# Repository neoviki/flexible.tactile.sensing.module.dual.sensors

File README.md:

# Flexible Tactile Sensing Module with Dual Sensors

## Description

This project features a **flexible tactile sensing module** equipped with **dual pressure sensors** designed to measure **tactile interaction**, specifically the pressure exerted by external forces. At the core of the module are two **BMP384 barometric pressure sensors** — MEMS (Micro-Electro-Mechanical Systems) sensors capable of measuring both **barometric pressure** and **temperature** with low power consumption. Their sensitivity makes them well-suited for tactile feedback and subtle pressure variation detection.

The **spacing between the two BMP384 sensors** is **3 millimeters**, allowing for localized differential pressure sensing. Both sensors communicate via the **I2C protocol**, ensuring straightforward integration with microcontroller boards such as the **Arduino Due**. The module operates at **3.3V**, and each sensor is assigned a unique I2C address to enable communication on the same bus:

- **Top Sensor**: `0x77`  
- **Bottom Sensor**: `0x76`

This tactile sensing module can be used in robotics, prosthetics, and human-machine interaction applications.

The **sensor module** is designed on a **flexible PCB**, making it adaptable to a wide range of environments where flexibility is essential. The design is created using **Eagle 7.7**, and the board is populated using **surface-mount technology (SMT)**. After population, the board has been tested with an **Arduino Due** to verify its sensor performance and sampling rate for tactile sensing applications.

## Project Structure

```
README.md
01.Documents                            # Essential documents used for this project
02.Schematics.and.Board.Layout.Design   # Contains the schematics and board layout files
03.Manufacturing                        # Contains CAM, DRU files, and other essential files for manufacturing
04.Populated.Board.Testing              # Contains Arduino code to test the tactile sensing module after population
05.Images                               # Contains a list of images
```

### Images

Here are some images related to the project, demonstrating the design and testing process:

1. **Populated Flexible Tactile Sensing Module**  

2. **Board Layout**  

3. **Schematics**  

4. **Fabricated Flexible PCB**  

---

## License

This project is licensed under the **BSD 2-Clause License**.  
See the [`LICENSE`](LICENSE) file for full license text.

## Usage and Attribution

You are welcome to **use, modify, or build upon this design** for personal, academic, or commercial purposes.  
If you use or adapt any part of this work, **please credit the original author**:

**V. Natarajan**

For academic usage, you may cite this repository using the following BibTeX entry:

```bibtex
@misc{vnatarajan_flexible_tactile_sensing_module_dual_sensors,
  author       = {V. Natarajan},
  title        = {Flexible Tactile Sensing Module with Dual Sensors},
  year         = {2025},
  howpublished = {\url{https://github.com/neoviki/flexible.tactile.sensing.module.dual.sensors}},
  note         = {Accessed: 2025-04-11}

}
```

> 📎 Attribution helps support and recognize open-source contributions — thank you!

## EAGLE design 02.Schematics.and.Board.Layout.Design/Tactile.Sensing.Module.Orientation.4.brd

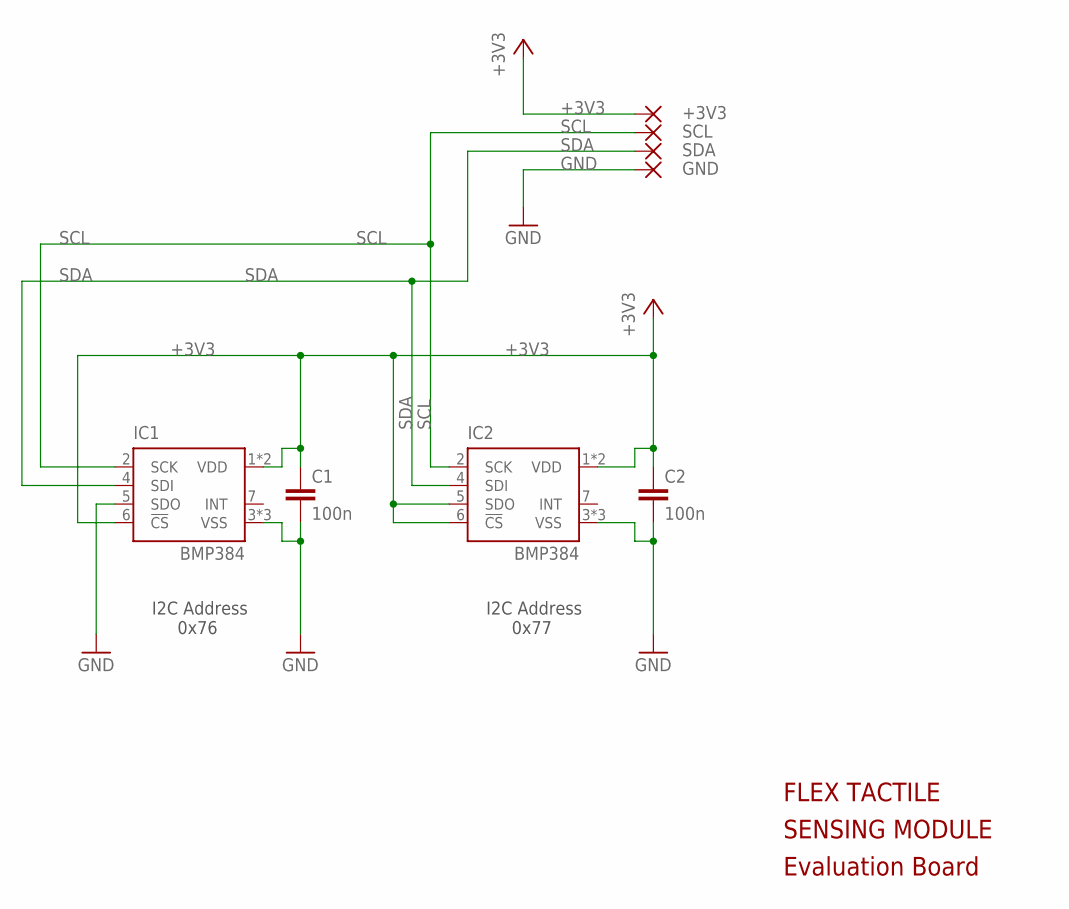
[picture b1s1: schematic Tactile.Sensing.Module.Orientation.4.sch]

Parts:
+3V3: SMD-PAD-2MMX4MM
C1, C2: 100n; C0201
GND: SMD-PAD-2MMX4MM
IC1, IC2: BMP384
SCL: SMD-PAD-2MMX4MM
SDA: SMD-PAD-2MMX4MM

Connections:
+3V3: +3V3.1, C1.1, C2.1, IC1.1 (VDD), IC1.6 (!CS), IC1.10 (VDD), IC2.1 (VDD), IC2.5 (SDO), IC2.6 (!CS), IC2.10 (VDD)
GND: C1.2, C2.2, GND.1, IC1.3 (VSS), IC1.5 (SDO), IC1.8 (VSS), IC1.9 (VSS), IC2.3 (VSS), IC2.8 (VSS), IC2.9 (VSS)
SCL: IC1.2 (SCK), IC2.2 (SCK), SCL.1
SDA: IC1.4 (SDI), IC2.4 (SDI), SDA.1

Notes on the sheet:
I2C Address 0x77
I2C Address 0x76
SENSING MODULE
Evaluation Board
FLEX TACTILE

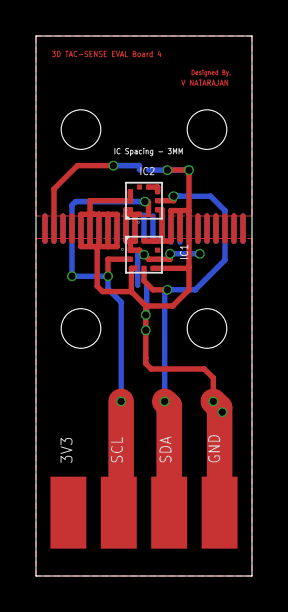
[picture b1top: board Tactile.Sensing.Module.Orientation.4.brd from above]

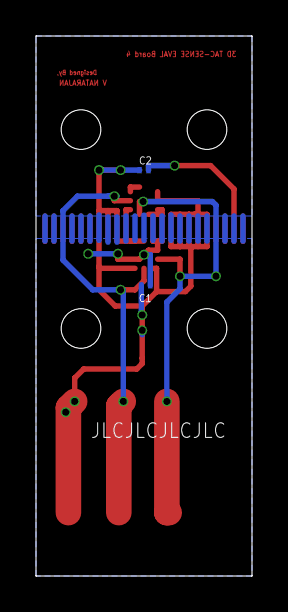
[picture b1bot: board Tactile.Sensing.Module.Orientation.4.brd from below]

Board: 2 copper layers, 12.0 x 30.0 mm, 8 parts (2 on the bottom side), 4 nets.

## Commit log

2025-04-11 auto
2026-02-26 Replace BSD License with GNU GPL v3
